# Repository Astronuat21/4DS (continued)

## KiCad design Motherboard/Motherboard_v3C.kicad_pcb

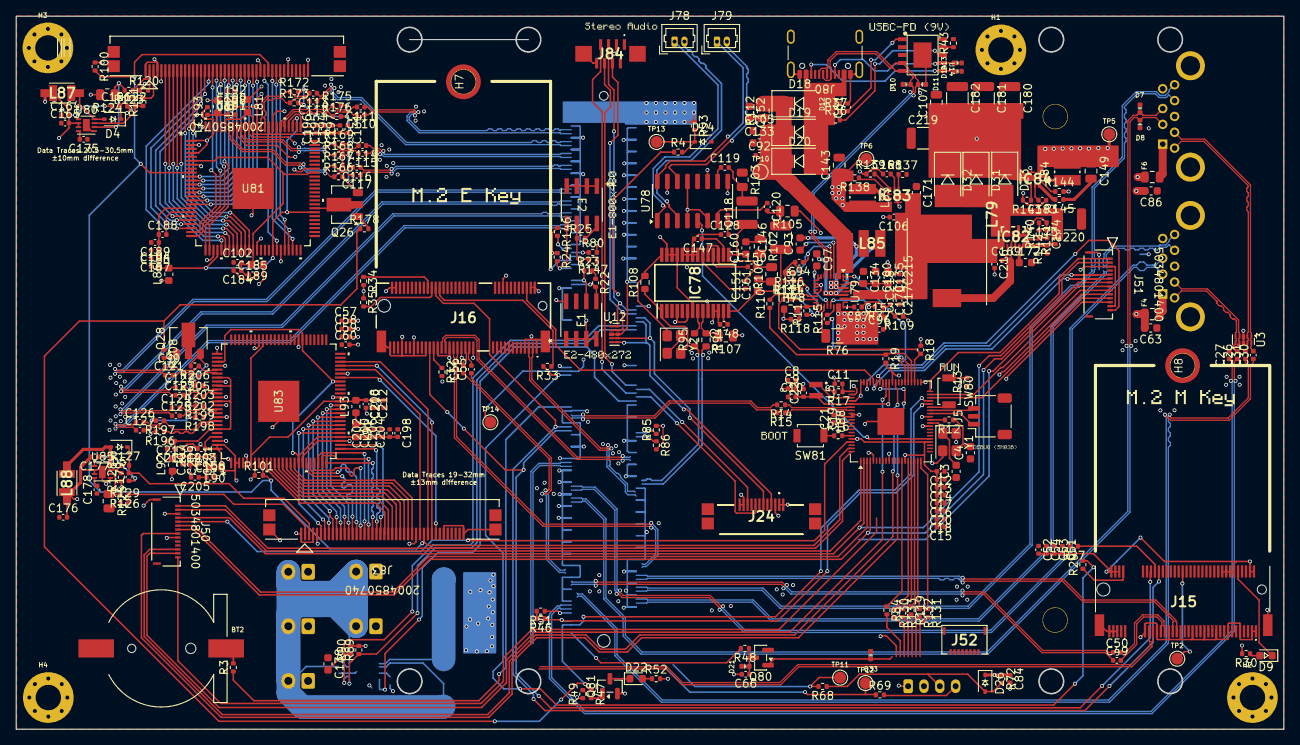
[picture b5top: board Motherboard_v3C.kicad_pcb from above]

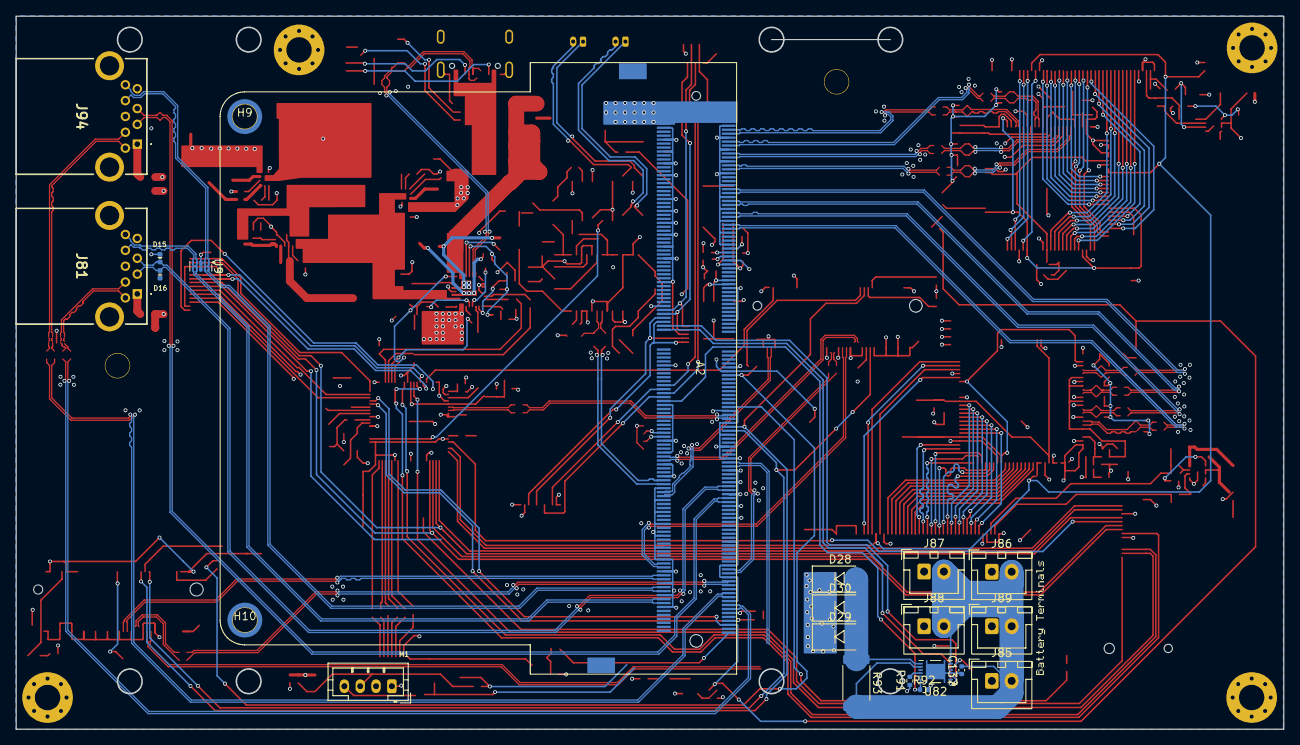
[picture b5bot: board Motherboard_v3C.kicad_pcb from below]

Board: 4 copper layers, 160.0 x 90.0 mm, 373 parts (23 on the bottom side), 327 nets.

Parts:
A2: LattePanda_Mu; LattePanda_Module_H8.0mm_Horizontal
BT2: Battery_Cell; Battery_Holder_CR1220_S8411-45R
C3, C4: 15pF; C_0603_1608Metric
C8, C9, C12, C13, C14, C15, C16, C17, C18, C20, C21, C26, C27, C30, C31, C52, C54, C58, C60, C84: 100nF; C_0402_1005Metric
C10, C11, C19, C22, C94: 4.7uF; C_0402_1005Metric
C49, C50, C55, C56, C169: 220nF; C_0402_1005Metric
C51, C53, C57, C59, C90, C96, C102, C104, C106, C108, C110, C111, C112, C113, C114, C115, C116, C117, C121, C122, C123, C124, C125, C126, C127, C131, C150, C153, C158, C164, C170, C177, C198, C207, C208, C215, C216, C217, C218: 10uF; C_0402_1005Metric
C61, C66, C119, C120, C128, C137, C147, C148, C151, C165, C166, C176, C179: 1uF; C_0402_1005Metric
C63, C86: 22uF; C_0603_1608Metric
C87: 1nF; C_0402_1005Metric
C92, C184, C185, C186, C187, C188, C189, C190, C191, C192, C193, C194, C195, C196, C197, C199, C200, C201, C202, C203, C204, C205, C206, C209, C210, C211, C212, C213, C214: 0.1uF; C_0402_1005Metric
C93, C97: 47nF; C_0603_1608Metric
C100, C105, C133, C134, C135: 10uF; C_0603_1608Metric
C107: 10uF; C_0805_2012Metric
C118, C146: 100uF; C_1210_3225Metric
C138: 0.47uF; C_0603_1608Metric
C143, C149: 22uF; C_0805_2012Metric
C152, C172: 2.2uF; C_0603_1608Metric
C160, C161: 0.022uF; C_0603_1608Metric
C168, C183: 1.2nF; C_0402_1005Metric
C171: 100nF; C_0603_1608Metric
C173: 39nF; C_0402_1005Metric
C174: 91pF; C_0402_1005Metric
C175, C178: 10nF; C_0402_1005Metric
C180, C181, C182, C219, C220: 47uF; C_1210_3225Metric
D4, D5, D26: 1N5819WS; D_SOD-323
D7, D8, D10, D11, D15, D16, D21, D33: ESD5V0B03; D_0402_1005Metric
D9, D22: LED_G; LED_0603_1608Metric
D12, D13, D14: PESD24VS1UL-N; D_0402_1005Metric
D18, D19, D20, D23, D28, D29, D30, D31, D32: SS54; D_SMA
D24: B5819WS-TP; D_SOD-323
E1, E2: 24AA025UIDT-I/SN; SOIC8-N_MC_MCH
F4, F6: 6V/2A; Fuse_0805_2012Metric
H1, H2, H3, H4: MountingHole_Pad; MountingHole_3.2mm_M3_Pad_Via
H7, H8: MountingHole_M2.0; MountingHole_3mm_M2_Pad_TopOnly
H9, H10: MountingHole_Pad; MountingHole_3mm_M2_Pad_TopOnly
IC78: PCM2704CDBR; SOP65P780X200-28N
IC82: TPS61288LRQQR; PTPS61288RQQR
IC83, IC84: TPS62903RPJR
J5: SM03B-SRSS-TB; JST_SH_SM03B-SRSS-TB_1x03-1MP_P1.00mm_Horizontal
J15: M.2 Socket M; MDT420M03001
J16: M.2 Socket E; MDT420E03001
J24: 200485-0710; 2004850710
J50, J51: 5034801400
J52: 503480-0800; 5034800800
J78: Speaker_L; Molex_PicoBlade_53047-0210_1x02_P1.25mm_Vertical
J79: Speaker_R; Molex_PicoBlade_53047-0210_1x02_P1.25mm_Vertical
J80: USB_C_Receptacle_USB2.0_16P; USB_C_Receptacle_GCT_USB4105-xx-A_16P_TopMnt_Horizontal
J81, J94: GSB311A41EU
J83, J90: 2004850740; CON_2004850740
J84: FFC2A33-08-T-R; FFC2A3308TR
J85: JST_XHP2_Battery1; JST_XH_B2B-XH-A_1x02_P2.50mm_Vertical
J86: JST_XHP2_Battery2; JST_XH_B2B-XH-A_1x02_P2.50mm_Vertical
J87: JST_XHP2_Battery3; JST_XH_B2B-XH-A_1x02_P2.50mm_Vertical
J88: JST_XHP2_Battery4; JST_XH_B2B-XH-A_1x02_P2.50mm_Vertical
J89: JST_XHP2_Battery5; JST_XH_B2B-XH-A_1x02_P2.50mm_Vertical
L5: 3.3uH; L_pol_2016
L79: 7443330220; WE-HCC_109021
L81, L82, L86, L89, L90, L91, L92, L93: BLM18RK601SN1D; L_0603_1608Metric
L83, L84: 74438336010HT
L85: 74438336022HT
L87, L88: LQH32CN220K23L; LQH32DN100K23L
M1: Fan_4pin; JST_PH_B4B-PH-K_1x04_P2.00mm_Vertical
Q26, Q28: 2SK3018-TP; SOT-89-3
Q80, Q81: 2N7002; SOT-23
R3, R12, R13, R16, R37, R47: 1k/1%; R_0402_1005Metric
R4, R18, R19, R22, R23, R24, R25, R34, R35, R36, R49, R85, R86, R91, R92, R100, R101, R109, R110, R111, R115: 10k/1%; R_0402_1005Metric
R14, R15: 27R; R_0402_1005Metric
R17: 33R/1%; R_0402_1005Metric
R27, R29, R32, R33: 0R/1%; R_0402_1005Metric
R30, R52, R53: 2.2k/1%; R_0402_1005Metric
R43: 6.8k/1%; R_0402_1005Metric
R46, R48, R69: 100R/1%; R_0402_1005Metric
R51, R80, R116, R138, R144: 100k/1%; R_0402_1005Metric
R68: 21.5K/1%; R_0402_1005Metric
R72: 4.7K/1%; R_0402_1005Metric
R76: 100R/1%; R_1206_3216Metric
R77: 4.7k/1%; R_0402_1005Metric
R84, R119: 150R/1%; R_0402_1005Metric
R89, R90: 5.1k/1%; R_0402_1005Metric
R93: 0.010R/1%; R_2512_6332Metric
R94, R95: 22R/1%; R_0603_1608Metric
R102, R106: 16R/1%; R_0805_2012Metric
R103, R105: 330R/1%; R_0805_2012Metric
R107: 1.5k/1%; R_0805_2012Metric
R108: 1M/1%; R_0603_1608Metric
R112: 2R/1%; R_0805_2012Metric
R113, R114: 127k/1%; R_0402_1005Metric
R117: 5.24k/1%; R_0402_1005Metric
R118: 30k/1%; R_0402_1005Metric
R120: 5.1R/1%; R_0402_1005Metric
R121, R122, R127, R128: 910k/1%; R_0402_1005Metric
R123, R126: 5k/1%; R_0402_1005Metric
R124, R125: 90.9k/1%; R_0805_2012Metric
R129: 10R/1%; R_0402_1005Metric
R130, R131, R132, R133: 47R/1%; R_0402_1005Metric
R137, R143: 40.2k/1%; R_0402_1005Metric
R139: 249k/1%; R_0402_1005Metric
R140: 39.2k/1%; R_0402_1005Metric
R141: 931k/1%; R_0402_1005Metric
R142: 48.7k/1%; R_0402_1005Metric
R145: 76.8k/1%; R_0402_1005Metric
R146, R147: 470R/1%; R_0402_1005Metric
R166, R167, R168, R169, R172, R173, R175, R176, R196, R197, R198, R199, R202, R203, R205, R206: 56k/1%; R_0402_1005Metric
R178, R208: 21.5k/1%; R_0402_1005Metric
SW80, SW81: SW_Push; SW_SPST_B3U-1000P
TH78: 10k/1%; R_0603_1608Metric
TP2, TP5, TP6, TP10, TP11, TP12, TP13, TP14: TestPoint; TestPoint_Pad_D1.5mm
U3, U9, U12: D3V3XA4B10LP-7; Diodes_UDFN-10_1x2.5mm_P0.5mm
U14: CH224K; ESSOP-10-1EP_3.9x5mm_P1.0mm_EP3.2x2.3
U78: PAM8406D; SOIC-16_3.9x9.9mm_P1.27mm
U79: BQ25798; Texas_RQM0029A_VQFN-29_4x4mm_P0.4mm
U80, U85: PAM2841G; DFN-8-1EP_2x2mm_P0.5mm_EP0.86x1.55mm
U81, U83: TFP401APZP; PZP100_5P2X5P2
U82: BQ27441DRZT-G1A; Texas_S-PDSO-N12
U88: RP2354B; QFN-80-1EP_10x10mm_P0.4mm_EP3.4x3.4mm
Y1, Y2: ABM8-272-T3; Crystal_SMD_3225-4Pin_3.2x2.5mm
kibuzzard-6A7CAF20: G***; kibuzzard-6A7CAF20
kibuzzard-6A7CAF29: G***; kibuzzard-6A7CAF29
kibuzzard-6A7CAF45: G***; kibuzzard-6A7CAF45
kibuzzard-6A7DF5CF: G***; kibuzzard-6A7DF5CF
kibuzzard-6A7DF57A: G***; kibuzzard-6A7DF57A
kibuzzard-6A9CE0FA: G***; kibuzzard-6A9CE0FA
kibuzzard-6A9CE105: G***; kibuzzard-6A9CE105
kibuzzard-6A74CEFD: G***; kibuzzard-6A74CEFD
kibuzzard-6A74CF1D: G***; kibuzzard-6A74CF1D
kibuzzard-6A760A01: G***; kibuzzard-6A760A01

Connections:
+1V1: C8.2, C9.2, C10.2, C22.1, L5.2, U88.10 (DVDD), U88.32 (DVDD), U88.51 (DVDD), U88.65 (VREG_FB)
+3V3: C12.2, C13.2, C14.2, C15.2, C16.2, C17.2, C18.2, C19.2, C20.2, C21.2, C51.2, C52.2, C53.2, C54.2, C57.2, C58.2, C59.2, C60.2, C143.1, C164.2, C165.2, C176.2, C177.2, E1.8, E2.8, IC78.7 (VDD), IC78.10 (VBUS), IC78.25 (TEST1), IC78.26 (TEST0), IC78.27 (~SSPND), IC83.3 (VOS), J15.2 (3.3V), J15.4 (3.3V), J15.12 (3.3V), J15.14 (3.3V), J15.16 (3.3V), J15.18 (3.3V), J15.70 (3.3V), J15.72 (3.3V), J15.74 (3.3V), J16.2 (3.3V), J16.4 (3.3V), J16.72 (3.3V), J16.74 (3.3V), J24.2, J50.3, J50.9, J51.3, J51.13, J83.4, J84.3, J90.4, L81.1, L82.1, L83.2, L86.1, L87.1, L87.3, L88.1, L88.3, L89.1, L90.1, L91.1, L92.1, L93.1, R17.2, R18.1, R19.2, R22.1, R23.2, R24.1, R25.2, R30.2, R34.2, R35.1, R52.2, R89.2, R90.2, R92.2, R100.1, R101.1, R107.1, R109.1, R138.2, R146.1, R147.1, TP6.1 (1_1), U78.4 (PVDDL), U78.6 (VDD), U78.9 (MODE), U78.13 (PVDDR), U80.2 (VIN), U80.3 (ENA), U81.2 (*PD), U81.3 (ST), U81.7 (*STAG), U81.99 (RSVD), U81.100 (OCK_INV), U83.2 (*PD), U83.3 (ST), U83.7 (*STAG), U83.99 (RSVD), U83.100 (OCK_INV), U85.2 (VIN), U85.3 (ENA), U88.5 (IOVDD), U88.15 (IOVDD), U88.24 (IOVDD), U88.29 (IOVDD), U88.41 (IOVDD), U88.50 (IOVDD), U88.59 (ADC_AVDD), U88.60 (IOVDD), U88.64 (VREG_VIN), U88.68 (USB_OTP_VDD), U88.69 (QSPI_IOVDD), U88.76 (IOVDD)
+5V: C63.2, C84.1, C86.2, C149.1, D26.1 (K), F4.1, F6.1, IC84.3 (VOS), L84.2, M1.2 (+), R72.1, R144.2, TP5.1 (1_1)
+9V: D12.1 (K), D18.2 (A), D19.2 (A), D20.2 (A), J80.A4 (VBUS), J80.A9 (VBUS), J80.B4 (VBUS), J80.B9 (VBUS), R36.1, R37.1
+BATT: A2.115 (VBAT), R3.1
/EXIO/Col1: J50.5, U88.77 (GPIO0)
/EXIO/Col2: J50.11, U88.78 (GPIO1)
/EXIO/Col3: J51.11, U88.38 (GPIO30)
/EXIO/Col4: J51.9, U88.39 (GPIO31)
/EXIO/LED_PWR_B: R131.1, U88.20 (GPIO20)
/EXIO/LED_PWR_G: R132.1, U88.19 (GPIO19)
/EXIO/LED_PWR_R: R119.1, U88.18 (GPIO18)
/EXIO/LED_WiFi_B: R133.1, U88.17 (GPIO17)
/EXIO/LED_WiFi_G: R130.1, U88.16 (GPIO16)
/EXIO/LED_WiFi_R: R84.1, U88.14 (GPIO15)
/EXIO/L_ADC_X: J50.13, U88.52 (GPIO41/ADC1)
/EXIO/L_ADC_Y: J50.12, U88.49 (GPIO40/ADC0)
/EXIO/PWR_Button: D33.1 (A1), J52.1, Q80.1 (G)
/EXIO/RPi_HALL_L: J50.1, U88.80 (GPIO3)
/EXIO/RPi_HALL_R: J51.1, U88.40 (GPIO32)
/EXIO/R_ADC_X: J51.5, U88.54 (GPIO43/ADC3)
/EXIO/R_ADC_Y: J51.6, U88.55 (GPIO44/ADC4)
/EXIO/Row1: J50.4, J51.2, U88.2 (GPIO5)
/EXIO/Row2: J50.7, J51.7, U88.4 (GPIO7)
/EXIO/Row3: J50.2, J51.8, U88.1 (GPIO4)
/EXIO/Row4: J50.6, J51.12, U88.3 (GPIO6)
/EXIO/Row5: J50.14, J51.10, U88.6 (GPIO8)
/EXIO/SL_BRI: J51.14, U88.58 (GPIO47/ADC7)
/EXIO/SL_VOL: J50.8, U88.53 (GPIO42/ADC2)
/Fan_Temp/FAN_1_PWM: A2.2 (FAN1_PWM), R69.1, TP12.1 (1_1)
/Fan_Temp/FAN_1_TAC: A2.4 (FAN1_TAC), R68.2, TP11.1 (1_1)
/LattePanda Module/AMP_L: C120.1, U78.7 (INL)
/LattePanda Module/AMP_R: C119.1, U78.10 (INR)
/LattePanda Module/Audio_D+: A2.76 (USB2_P7+), R94.2
/LattePanda Module/Audio_D-: A2.78 (USB2_P7-), R95.1
/LattePanda Module/Audio_DX+: IC78.9 (D+), R94.1, R107.2
/LattePanda Module/Audio_DX-: IC78.8 (D-), R95.2
/LattePanda Module/DDIB_INT: A2.124 (GPP_F13), J24.9
/LattePanda Module/DDIB_RST: A2.120 (GPP_F15), J24.7
/LattePanda Module/DDIB_TOUCH_SCL: A2.150 (I2C3_SCL), J24.3, U12.5, U12.6 (NC)
/LattePanda Module/DDIB_TOUCH_SDA: A2.152 (I2C3_SDA), J24.5, U12.4, U12.7 (NC)
/LattePanda Module/DDIB_TX0+: A2.217 (DDIB_TX0+), C90.1
/LattePanda Module/DDIB_TX0-: A2.215 (DDIB_TX0-), C121.1
/LattePanda Module/DDIB_TX1+: A2.211 (DDIB_TX1+), C122.1
/LattePanda Module/DDIB_TX1-: A2.209 (DDIB_TX1-), C123.1
/LattePanda Module/DDIB_TX2+: A2.205 (DDIB_TX2+), C124.1
/LattePanda Module/DDIB_TX2-: A2.203 (DDIB_TX2-), C125.1
/LattePanda Module/DDIB_TX3+: A2.199 (DDIB_TX3+), C126.1
/LattePanda Module/DDIB_TX3-: A2.197 (DDIB_TX3-), C127.1
/LattePanda Module/HSIO_0_TX+: A2.13 (HSIO0_TX+), C27.1
/LattePanda Module/HSIO_0_TX-: A2.15 (HSIO0_TX-), C26.1
/LattePanda Module/HSIO_1_TX+: A2.19 (HSIO1_TX+), C31.1
/LattePanda Module/HSIO_1_TX-: A2.21 (HSIO1_TX-), C30.1
/LattePanda Module/HSIO_2_RX+: A2.28 (HSIO2_RX+), J15.43 (PERp0/SATA-B-)
/LattePanda Module/HSIO_2_RX-: A2.30 (HSIO2_RX-), J15.41 (PERn0/SATA-B+)
/LattePanda Module/HSIO_2_TX+: A2.25 (HSIO2_TX+), C49.1
/LattePanda Module/HSIO_2_TX-: A2.27 (HSIO2_TX-), C50.1
/LattePanda Module/HSIO_3_RX+: A2.34 (HSIO3_RX+), J16.41 (PERp0)
/LattePanda Module/HSIO_3_RX-: A2.36 (HSIO3_RX-), J16.43 (PERn0)
/LattePanda Module/HSIO_3_TX+: A2.31 (HSIO3_TX+), C55.1
/LattePanda Module/HSIO_3_TX-: A2.33 (HSIO3_TX-), C56.1
/LattePanda Module/LOUT+: J78.1, U78.1 (+OUT_L)
/LattePanda Module/LOUT-: J78.2, U78.3 (-OUT_L)
/LattePanda Module/REFCLK0+: A2.85 (REFCLK0+), J15.53 (REFCLKn)
/LattePanda Module/REFCLK0-: A2.87 (REFCLK0-), J15.55 (REFCLKp)
/LattePanda Module/REFCLK3+: A2.88 (REFCLK3+), J16.47 (REFCLKp0)
/LattePanda Module/REFCLK3-: A2.90 (REFCLK3-), J16.49 (REFCLKn0)
/LattePanda Module/ROUT+: J79.1, U78.16 (+OUT_R)
/LattePanda Module/ROUT-: J79.2, U78.14 (-OUT_R)
/LattePanda Module/RP+: R14.1, U88.66 (USB_DM)
/LattePanda Module/RP-: R15.1, U88.67 (USB_DP)
/LattePanda Module/RPI_BAT_GPO: A2.118 (GPP_F16), R92.1, U82.12 (GPOUT)
/LattePanda Module/RPI_BAT_SCL: A2.146 (I2C4_SCL), R89.1, U82.1 (SDA)
/LattePanda Module/RPI_BAT_SDA: A2.148 (I2C4_SDA), R90.1, U82.2 (SCL)
/LattePanda Module/RPI_BAT_STAT: R109.2, U79.1 (STAT), U88.46 (GPIO37)
/LattePanda Module/RPR+: A2.111 (USB2_P5+), R14.2
/LattePanda Module/RPR-: A2.109 (USB2_P5-), R15.2
/LattePanda Module/RPi_5A_INT: R115.1, U88.45 (GPIO36)
/LattePanda Module/RPi_5A_SCL: R19.1, R110.1, U88.44 (GPIO35)
/LattePanda Module/RPi_5A_SDA: R18.2, R111.1, U88.43 (GPIO34)
/LattePanda Module/RPi_LCD_EN: J83.31, J90.31, R100.2, R101.2, U81.8 (SCDT), U81.9 (*PDO), U83.8 (SCDT), U83.9 (*PDO), U88.79 (GPIO2)
/LattePanda Module/RPi_PAM_LPWR: U78.5 (~MUTE), U88.25 (GPIO24)
/LattePanda Module/SLS_S3: A2.7 (SLS_S3), R46.1, U88.36 (GPIO28)
/LattePanda Module/SUSCLK_WIFI: A2.131 (SUSCLK), R29.2, R33.2
/LattePanda Module/SWCLK: J5.1, U88.33 (SWCLK)
/LattePanda Module/SWD: J5.3, U88.34 (SWDIO)
/LattePanda Module/TCP0_INT: A2.126 (GPP_F12), J84.6
/LattePanda Module/TCP0_RST: A2.122 (GPP_F14), J84.7
/LattePanda Module/TCP0_TOUCH_SCL: A2.154 (I2C2_SCL), J84.4, U12.2, U12.9 (NC)
/LattePanda Module/TCP0_TOUCH_SDA: A2.156 (I2C2_SDA), J84.5, U12.1, U12.10 (NC)
/LattePanda Module/TCP0_TX0+: A2.247 (TCP0_TX0+), C110.1
/LattePanda Module/TCP0_TX0-: A2.245 (TCP0_TX0-), C111.1
/LattePanda Module/TCP0_TX1+: A2.241 (TCP0_TXRX0+), C112.1
/LattePanda Module/TCP0_TX1-: A2.239 (TCP0_TXRX0-), C113.1
/LattePanda Module/TCP0_TX2+: A2.235 (TCP0_TX1+), C114.1
/LattePanda Module/TCP0_TX2-: A2.233 (TCP0_TX1-), C115.1
/LattePanda Module/TCP0_TX3+: A2.229 (TCP0_TXRX1+), C116.1
/LattePanda Module/TCP0_TX3-: A2.227 (TCP0_TXRX1-), C117.1
/LattePanda Module/USB_2_P7+: A2.70 (USB2_P4+), J16.3 (USB_D+)
/LattePanda Module/USB_2_P7-: A2.72 (USB2_P4-), J16.5 (USB_D-)
/LattePanda Module/WiFi_M2E_LED: J16.6 (~LED_1), U88.56 (GPIO45/ADC5)
/LattePanda Module/~PWR_SW: A2.1 (~PWRBTN), R48.2
/LattePanda Module/~USB_BOOT: R16.1, SW81.1
/M.2 E&M Key/CON_PCIE_TX_0+: C55.2, J16.35 (PETp0)
/M.2 E&M Key/CON_PCIE_TX_0-: C56.2, J16.37 (PETn0)
/M.2 E&M Key/CON_PCIE_TX_1+: C49.2, J15.49 (PETp0/SATA-A+)
/M.2 E&M Key/CON_PCIE_TX_1-: C50.2, J15.47 (PETn0/SATA-A-)
/M.2 E&M Key/~CLKREQE: J16.53 (~CLKREQ0), R32.1
/M.2 E&M Key/~CLKREQM: J15.52 (~CLKREQ), R27.1
/PSU/12VIn: C220.2, D23.2 (A), D31.2 (A), D32.2 (A), IC82.5 (VOUT), IC82.13 (VOUT), R141.2
/PSU/BAT+: C96.1, C153.1, D28.1 (K), D29.1 (K), D30.1 (K), R76.1, U79.22 (BAT), U79.23 (BAT)
/PSU/B_RAW: C137.2, J85.2, J86.2, J87.2, J88.2, J89.2, R93.2, U82.6 (BAT), U82.8 (SRP)
/PSU/CC1: D13.1 (K), J80.A5 (CC1), U14.7 (CC1)
/PSU/CC2: D14.1 (K), J80.B5 (CC2), U14.6 (CC2)
/PSU/PWR_C_D+: D11.2 (A2), J80.A6 (D+), J80.B6 (D+), U14.4 (DP), U79.6 (D+)
/PSU/PWR_C_D-: D10.2 (A2), J80.A7 (D-), J80.B7 (D-), U14.5 (DM), U79.7 (D-)
/PSU/SYS: C106.1, C170.1, C171.2, C215.1, C216.1, C217.1, C218.1, IC82.6 (EN), IC82.7 (VIN), IC82.14 (VIN), IC83.5 (EN), IC83.6 (VIN), L79.1, U79.25 (SYS)
/RGB/B0: J83.5, U83.30 (QE16)
/RGB/B1: J83.6, U83.31 (QE17)
/RGB/B2: J83.7, U83.32 (QE18)
/RGB/B3: J83.8, U83.33 (QE19)
/RGB/B4: J83.9, U83.34 (QE20)
/RGB/B5: J83.10, U83.35 (QE21)
/RGB/B6: J83.11, U83.36 (QE22)
/RGB/B7: J83.12, U83.37 (QE23)
/RGB/B8: J83.13, U83.20 (QE8)
/RGB/B9: J83.14, U83.21 (QE9)
/RGB/B10: J83.15, U83.22 (QE10)
/RGB/B11: J83.16, U83.23 (QE11)
/RGB/B12: J83.17, U83.24 (QE12)
/RGB/B13: J83.18, U83.25 (QE13)
/RGB/B14: J83.19, U83.26 (QE14)
/RGB/B15: J83.20, U83.27 (QE15)
/RGB/B16: J83.21, U83.10 (QE0)
/RGB/B17: J83.22, U83.11 (QE1)
/RGB/B18: J83.23, U83.12 (QE2)
/RGB/B19: J83.24, U83.13 (QE3)
/RGB/B20: J83.25, U83.14 (QE4)
/RGB/B21: J83.26, U83.15 (QE5)
/RGB/B22: J83.27, U83.16 (QE6)
/RGB/B23: J83.28, U83.17 (QE7)
/RGB/B-AVDD: C207.2, C209.1, C211.1, C213.1, C214.1, L92.2, U83.82 (AVDD), U83.84 (AVDD), U83.88 (AVDD), U83.95 (AVDD)
/RGB/B-DE: J83.30, U83.46 (DE)
/RGB/B-DVDD: C208.2, C210.1, C212.1, L93.2, U83.6 (DVDD), U83.38 (DVDD), U83.67 (DVDD)
/RGB/B-HS: J83.32, U83.48 (HSYNC)
/RGB/B-OVDD: C198.2, C200.1, C202.1, C204.1, C206.1, L91.2, U83.18 (OVDD), U83.29 (OVDD), U83.43 (OVDD), U83.57 (OVDD), U83.78 (OVDD)
/RGB/B-PCK: J83.34, U83.44 (ODCK)
/RGB/B-PVDD: C158.2, C199.1, C201.1, C203.1, C205.1, L90.2, U83.97 (PVDD)
/RGB/B-VS: J83.33, U83.47 (VSYNC)
/RGB/DDIB_CK+: C126.2, R197.1, U83.93 (RXC+)
/RGB/DDIB_CK-: C127.2, R196.1, U83.94 (RXC-)
/RGB/DDIB_D0+: C124.2, R199.1, U83.90 (RX0+)
/RGB/DDIB_D0-: C125.2, R198.1, U83.91 (RX0-)
/RGB/DDIB_D1+: C122.2, R203.1, U83.85 (RX1+)
/RGB/DDIB_D1-: C123.2, R202.1, U83.86 (RX1-)
/RGB/DDIB_D2+: C90.2, R206.1, U83.80 (RX2+)
/RGB/DDIB_D2-: C121.2, R205.1, U83.81 (RX2-)
/RGB/P0: J90.5, U81.30 (QE16)
/RGB/P1: J90.6, U81.31 (QE17)
/RGB/P2: J90.7, U81.32 (QE18)
/RGB/P3: J90.8, U81.33 (QE19)
/RGB/P4: J90.9, U81.34 (QE20)
/RGB/P5: J90.10, U81.35 (QE21)
/RGB/P6: J90.11, U81.36 (QE22)
/RGB/P7: J90.12, U81.37 (QE23)
/RGB/P8: J90.13, U81.20 (QE8)
/RGB/P9: J90.14, U81.21 (QE9)
/RGB/P10: J90.15, U81.22 (QE10)
/RGB/P11: J90.16, U81.23 (QE11)
/RGB/P12: J90.17, U81.24 (QE12)
/RGB/P13: J90.18, U81.25 (QE13)
/RGB/P14: J90.19, U81.26 (QE14)
/RGB/P15: J90.20, U81.27 (QE15)
/RGB/P16: J90.21, U81.10 (QE0)
/RGB/P17: J90.22, U81.11 (QE1)
/RGB/P18: J90.23, U81.12 (QE2)
/RGB/P19: J90.24, U81.13 (QE3)
/RGB/P20: J90.25, U81.14 (QE4)
/RGB/P21: J90.26, U81.15 (QE5)
/RGB/P22: J90.27, U81.16 (QE6)
/RGB/P23: J90.28, U81.17 (QE7)
/RGB/P-AVDD: C131.2, C194.1, C195.1, C196.1, C197.1, L81.2, U81.82 (AVDD), U81.84 (AVDD), U81.88 (AVDD), U81.95 (AVDD)
/RGB/P-DE: J90.34, U81.46 (DE)
/RGB/P-DVDD: C102.2, C184.1, C185.1, L89.2, U81.6 (DVDD), U81.38 (DVDD), U81.67 (DVDD)
/RGB/P-HS: J90.32, U81.48 (HSYNC)
/RGB/P-OVDD: C104.2, C186.1, C187.1, C188.1, C189.1, L86.2, U81.18 (OVDD), U81.29 (OVDD), U81.43 (OVDD), U81.57 (OVDD), U81.78 (OVDD)
/RGB/P-PCK: J90.30, U81.44 (ODCK)
/RGB/P-PVDD: C108.2, C190.1, C191.1, C192.1, C193.1, L82.2, U81.97 (PVDD)
/RGB/P-VS: J90.33, U81.47 (VSYNC)
/RGB/TMDS_CK+: C116.2, R167.1, U81.93 (RXC+)
/RGB/TMDS_CK-: C117.2, R166.1, U81.94 (RXC-)
/RGB/TMDS_D0+: C114.2, R169.1, U81.90 (RX0+)
/RGB/TMDS_D0-: C115.2, R168.1, U81.91 (RX0-)
/RGB/TMDS_D1+: C112.2, R173.1, U81.85 (RX1+)
/RGB/TMDS_D1-: C113.2, R172.1, U81.86 (RX1-)
/RGB/TMDS_D2+: C110.2, R176.1, U81.80 (RX2+)
/RGB/TMDS_D2-: C111.2, R175.1, U81.81 (RX2-)
/USB/CON_USB3_D_N: A2.73 (USB2_P2-), D16.2 (A2), J81.2 (D-)
/USB/CON_USB3_D_P: A2.75 (USB2_P2+), D15.2 (A2), J81.3 (D+)
/USB/CON_USB3_SSRX_N: A2.18 (HSIO0_RX-), J81.5 (STDA_SSRX-), U9.4, U9.7 (NC)
/USB/CON_USB3_SSRX_P: A2.16 (HSIO0_RX+), J81.6 (STDA_SSRX+), U9.5, U9.6 (NC)
/USB/CON_USB3_SSTX_N: C26.2, J81.8 (STDA_SSTX-), U3.4, U3.7 (NC)
/USB/CON_USB3_SSTX_P: C27.2, J81.9 (STDA_SSTX+), U3.5, U3.6 (NC)
/USB/CON_USB4_D_N: A2.67 (USB2_P1-), D8.2 (A2), J94.2 (D-)
/USB/CON_USB4_D_P: A2.69 (USB2_P1+), D7.2 (A2), J94.3 (D+)
/USB/CON_USB4_SSRX_N: A2.24 (HSIO1_RX-), J94.5 (STDA_SSRX-), U9.1, U9.10 (NC)
/USB/CON_USB4_SSRX_P: A2.22 (HSIO1_RX+), J94.6 (STDA_SSRX+), U9.2, U9.9 (NC)
/USB/CON_USB4_SSTX_N: C30.2, J94.8 (STDA_SSTX-), U3.1, U3.10 (NC)
/USB/CON_USB4_SSTX_P: C31.2, J94.9 (STDA_SSTX+), U3.2, U3.9 (NC)
/~PLT_RST: A2.105 (~PLTRST), J15.50 (~PERST), J16.52 (~PERST0)
/~PWR_LED/~PSON: A2.5 (SLS_S0), R47.1, R178.1, R208.1, U88.37 (GPIO29)
/~WAKE: A2.103 (~WAKE), J15.54 (~PEWAKE), J16.55 (~PEWAKE0)
GND: A2.11 (GND), A2.14 (GND), A2.17 (GND), A2.20 (GND), A2.23 (GND), A2.26 (GND), A2.29 (GND), A2.32 (GND), A2.35 (GND), A2.38 (GND), A2.41 (GND), A2.44 (GND), A2.47 (GND), A2.50 (GND), A2.53 (GND), A2.56 (GND), A2.59 (GND), A2.62 (GND), A2.65 (GND), A2.68 (GND), A2.71 (GND), A2.74 (GND), A2.77 (GND), A2.80 (GND), A2.83 (GND), A2.86 (GND), A2.89 (GND), A2.92 (GND), A2.95 (GND), A2.98 (GND), A2.101 (GND), A2.107 (GND), A2.110 (GND), A2.113 (GND), A2.116 (GND), A2.135 (GND), A2.136 (GND), A2.151 (GND), A2.158 (GND), A2.167 (GND), A2.170 (GND), A2.181 (GND), A2.182 (GND), A2.188 (GND), A2.189 (GND), A2.194 (GND), A2.195 (GND), A2.200 (GND), A2.201 (GND), A2.206 (GND), A2.207 (GND), A2.212 (GND), A2.213 (GND), A2.218 (GND), A2.219 (GND), A2.224 (GND), A2.225 (GND), A2.230 (GND), A2.231 (GND), A2.236 (GND), A2.237 (GND), A2.242 (GND), A2.243 (GND), A2.248 (GND), A2.249 (GND), A2.MP (Mountinge_Pads), BT2.2 (-), C3.1, C4.1, C8.1, C9.1, C10.1, C11.1, C12.1, C13.1, C14.1, C15.1, C16.1, C17.1, C18.1, C19.1, C20.1, C21.1, C22.2, C51.1, C52.1, C53.1, C54.1, C57.1, C58.1, C59.1, C60.1, C61.2, C63.1, C66.2, C84.2, C86.1, C87.1, C92.1, C94.2, C96.2, C100.1, C102.1, C104.1, C105.1, C106.2, C107.2, C108.1, C128.1, C131.1, C133.1, C134.1, C135.1, C137.1, C138.1, C143.2, C147.2, C148.2, C150.2, C151.2, C152.1, C153.2, C158.1, C165.1, C168.1, C170.2, C171.1, C172.2, C173.1, C174.1, C175.1, C176.1, C178.1, C180.1, C181.1, C182.1, C183.1, C184.2, C185.2, C186.2, C187.2, C188.2, C189.2, C190.2, C191.2, C192.2, C193.2, C194.2, C195.2, C196.2, C197.2, C198.1, C199.2, C200.2, C201.2, C202.2, C203.2, C204.2, C205.2, C206.2, C207.1, C208.1, C209.2, C210.2, C211.2, C212.2, C213.2, C214.2, C215.2, C216.2, C217.2, C218.2, C219.1, C220.1, D7.1 (A1), D8.1 (A1), D10.1 (A1), D11.1 (A1), D12.2 (A), D13.2 (A), D14.2 (A), D15.1 (A1), D16.1 (A1), D21.1 (A1), D24.2 (A), D33.2 (A2), E1.1, E1.2, E1.3, E1.4, E2.1, E2.2, E2.3, E2.4, H1.1 (1_1), H2.1 (1_1), H3.1 (1_1), H4.1 (1_1), H7.1 (1_1), H8.1 (1_1), H9.1 (1_1), H10.1 (1_1), IC78.4 (PSEL), IC78.6 (DGND), IC78.11 (ZGND), IC78.12 (AGNDL), IC78.17 (AGNDR), IC78.19 (PGND), IC78.21 (HOST), IC78.22 (HID0/MS), IC78.23 (HID1/MC), IC78.24 (HID2/MD), IC82.3 (PGND), IC82.10 (AGND), IC82.12 (PGND), IC83.4 (GND), IC84.4 (GND), J5.2, J5.MP (MountPin), J15.1 (GND), J15.3 (GND), J15.9 (GND), J15.15 (GND), J15.21 (GND), J15.27 (GND), J15.33 (GND), J15.39 (GND), J15.45 (GND), J15.51 (GND), J15.57 (GND), J15.71 (GND), J15.73 (GND), J15.75 (GND), J15.MP1, J15.MP2, J16.1 (GND), J16.7 (GND), J16.18 (GND), J16.33 (GND), J16.39 (GND), J16.45 (GND), J16.51 (GND), J16.57 (GND), J16.63 (GND), J16.69 (GND), J16.75 (GND), J16.MP1, J16.MP2, J24.1, J24.10, J24.G1 (GND_1), J24.G2 (GND_2), J24.MP1, J24.MP2, J24.MP3, J24.MP4, J50.10, J50.P1, J50.P2, J51.4, J51.P1, J51.P2, J52.2, J52.9, J52.10, J80.A1 (GND), J80.A12 (GND), J80.B1 (GND), J80.B12 (GND), J80.SH (SHIELD), J81.4 (GND), J81.7 (GND_DRAIN), J81.MH1, J81.MH2, J83.3, J83.29, J83.36, J83.G1, J83.G2, J83.P1, J83.P2, J83.P3, J83.P4, J84.1, J84.8, J84.MP1, J84.MP2, J85.1, J86.1, J87.1, J88.1, J89.1, J90.3, J90.29, J90.36, J90.G1, J90.G2, J90.P1, J90.P2, J90.P3, J90.P4, J94.4 (GND), J94.7 (GND_DRAIN), J94.MH1, J94.MH2, M1.1 (-), Q26.2 (S), Q28.2 (S), Q80.2 (S), Q81.2 (S), R13.1, R27.2, R32.2, R43.2, R49.1, R51.1, R77.1, R80.2, R85.2, R86.2, R91.1, R102.2, R103.1, R105.1, R106.2, R114.2, R116.2, R118.2, R120.1, R122.1, R124.2, R125.2, R128.1, R129.1, R137.2, R139.1, R142.1, R143.2, SW81.2, TH78.1, U3.3 (VSS), U3.8 (VSS), U9.3 (VSS), U9.8 (VSS), U12.3 (VSS), U12.8 (VSS), U14.0 (GND), U78.2 (PGNDL), U78.11 (GND), U78.15 (PGNDR), U79.10 (ACDRV2), U79.11 (ACDRV1), U79.13 (~CE), U79.27 (GND), U80.5 (GND), U80.9 (GND), U81.1 (DFO), U81.4 (PIXS), U81.5 (GND), U81.19 (OGND), U81.28 (OGND), U81.39 (GND), U81.45 (OGND), U81.58 (OGND), U81.68 (GND), U81.76 (OGND), U81.79 (AGND), U81.83 (AGND), U81.87 (AGND), U81.89 (AGND), U81.92 (AGND), U81.98 (PGND), U81.PAD, U82.3 (V_{SS}), U82.13 (PAD), U83.1 (DFO), U83.4 (PIXS), U83.5 (GND), U83.19 (OGND), U83.28 (OGND), U83.39 (GND), U83.45 (OGND), U83.58 (OGND), U83.68 (GND), U83.76 (OGND), U83.79 (AGND), U83.83 (AGND), U83.87 (AGND), U83.89 (AGND), U83.92 (AGND), U83.98 (PGND), U83.PAD, U85.5 (GND), U85.9 (GND), U88.62 (VREG_PGND), U88.81 (GND), Y1.2, Y1.4, Y2.2, Y2.4
LED_SCB+: C179.2, D5.1 (K), J83.2, R127.2
LED_SCB-: J83.1, R126.1, R129.2
LED_SCT+: C166.2, D4.1 (K), J90.2, R121.2
LED_SCT-: J90.1, R120.2, R123.1
unnamed: A2.171 (DDIB_DDC_SCL), E1.6, R23.1
unnamed: A2.169 (DDIB_DDC_SDA), E1.5, R22.2
unnamed: A2.183 (DDIB_HPD), R147.2
unnamed: A2.179 (TCP0_DDC_SCL), E2.6, R25.1
unnamed: A2.177 (TCP0_DDC_SDA), E2.5, R24.2
unnamed: A2.187 (TCP0_HPD), R146.2
unnamed: A2.185 (TCP1_HPD), R80.1
unnamed: A2.133 (~BIOS_SEL), R4.1, TP14.1 (1_1)
unnamed: A2.100 (~CLKREQ3), R86.1
unnamed: A2.102 (~CLKREQ4), R85.1
unnamed: BT2.1 (+), R3.2
unnamed: C4.2, R12.1, Y1.3
unnamed: C118.2, C119.2, R103.2
unnamed: C120.2, C146.2, R105.2
unnamed: C149.2, R145.1
unnamed: C152.2, R112.1
unnamed: C160.2, R102.1
unnamed: C161.2, R106.1
unnamed: C169.2, IC82.4 (SW), IC82.9 (SW), L79.2
unnamed: C173.2, R140.2
unnamed: D4.2 (A), L87.2, L87.4, U80.8 (SW)
unnamed: D5.2 (A), L88.2, L88.4, U85.8 (SW)
unnamed: D9.2 (A), R30.1
unnamed: D9.1 (K), J15.10 (DAS/~DSS/~LED1)
unnamed: C92.2, C105.2, C133.2, D18.1 (K), D19.1 (K), D20.1 (K), R112.2, TP10.1 (1_1), U79.2 (VBUS), U79.3 (VBUS)
unnamed: D22.2 (A), R52.1
unnamed: D22.1 (K), Q81.3 (D)
unnamed: D26.2 (A), M1.3 (Tacho), R68.1, R72.2
unnamed: D28.2 (A), D29.2 (A), D30.2 (A), R93.1, U82.7 (SRN)
unnamed: C148.1, IC78.13 (VCCL)
unnamed: C151.1, IC78.20 (VCCP)
unnamed: C147.1, IC78.16 (VCCR)
unnamed: C150.1, IC78.18 (VCOM)
unnamed: C146.1, C161.1, IC78.14 (VOUTL)
unnamed: C118.1, C160.1, IC78.15 (VOUTR)
unnamed: IC78.28 (XTI), R108.2, Y2.1
unnamed: IC78.1 (XTO), R108.1, Y2.3
unnamed: C169.1, IC82.8 (BST)
unnamed: C174.2, IC82.2 (COMP), R140.1
unnamed: IC82.1 (FB), IC82.15 (FB), R141.1, R142.2
unnamed: C172.1, IC82.11 (VCC)
unnamed: IC83.9 (FB/VSET), R139.2
unnamed: IC83.7 (MODE/S-CONF), R137.1
unnamed: IC83.1 (PG), R138.1
unnamed: C168.2, IC83.8 (SS/TR)
unnamed: IC83.2 (SW), L83.1
unnamed: IC84.9 (FB/VSET), R145.2
unnamed: IC84.7 (MODE/S-CONF), R143.1
unnamed: IC84.1 (PG), R144.1
unnamed: C183.2, IC84.8 (SS/TR)
unnamed: IC84.2 (SW), L84.1
unnamed: J15.38 (DEVSLP), TP2.1 (1_1)
unnamed: J15.68 (SUSCLK), R29.1
unnamed: J16.50 (SUSCLK), R33.1
unnamed: J16.56 (~W_DISABLE1), R34.1
unnamed: J16.54 (~W_DISABLE2), R35.2
unnamed: J52.3, R84.2
unnamed: J52.4, R130.2
unnamed: J52.5, R133.2
unnamed: J52.6, R119.2
unnamed: J52.7, R132.2
unnamed: J52.8, R131.2
unnamed: F4.2, J81.1 (VBUS)
unnamed: F6.2, J94.1 (VBUS)
unnamed: M1.4 (PWM), R69.2
unnamed: Q26.3 (D), R166.2, R167.2, R168.2, R169.2, R172.2, R173.2, R175.2, R176.2
unnamed: Q26.1 (G), R178.2
unnamed: Q28.3 (D), R196.2, R197.2, R198.2, R199.2, R202.2, R203.2, R205.2, R206.2
unnamed: Q28.1 (G), R208.2
unnamed: Q81.1 (G), R47.2, R49.2
unnamed: R13.2, SW80.1
unnamed: R46.2, R51.2
unnamed: R43.1, U14.9 (CFG1)
unnamed: R36.2, U14.8 (VBUS)
unnamed: C61.1, R37.2, U14.1 (VDD)
unnamed: C128.2, U78.8 (VREF)
unnamed: R76.2, U79.18 (BATP)
unnamed: C93.1, U79.4 (BTST1)
unnamed: C97.2, U79.19 (BTST2)
unnamed: R113.2, R114.1, R116.1, U79.17 (ILIM_HIZ)
unnamed: C100.2, C134.2, C135.2, U79.29 (PMID)
unnamed: R77.2, U79.20 (PROG)
unnamed: C94.1, R113.1, R117.1, U79.5 (REGN)
unnamed: R110.2, U79.14 (SCL)
unnamed: R111.2, U79.15 (SDA)
unnamed: C87.2, U79.24 (SDRV)
unnamed: C93.2, L85.1, U79.28 (SW1)
unnamed: C97.1, L85.2, U79.26 (SW2)
unnamed: R117.2, R118.1, TH78.2, U79.16 (TS)
unnamed: U79.8 (VAC2), U79.9 (VAC1)
unnamed: R115.2, U79.21 (~INT)
unnamed: C175.2, U80.4 (Comp)
unnamed: R123.2, R124.1, U80.6 (FB)
unnamed: R121.1, R122.2, U80.7 (OVP)
unnamed: R91.2, U82.10 (BIN)
unnamed: C138.2, U82.5 (V_{DD})
unnamed: C178.2, U85.4 (Comp)
unnamed: R125.1, R126.2, U85.6 (FB)
unnamed: R127.1, R128.2, U85.7 (OVP)
unnamed: SW80.2, U88.35 (RUN)
unnamed: C11.2, R17.1, U88.61 (VREG_AVDD)
unnamed: L5.1, U88.63 (VREG_LX)
unnamed: C3.2, U88.30 (XIN), Y1.1
unnamed: R12.2, U88.31 (XOUT)
unnamed: R16.2, U88.75 (~QSPI_SS)
PGND_B: C177.1, C179.1, U85.1 (PGND)
PGND_T: C164.1, C166.1, U80.1 (PGND)
PWR: C66.1, D21.2 (A2), Q80.3 (D), R48.1
VDC: A2.250 (VIN), A2.251 (VIN), A2.252 (VIN), A2.253 (VIN), A2.254 (VIN), A2.255 (VIN), A2.256 (VIN), A2.257 (VIN), A2.258 (VIN), A2.259 (VIN), A2.260 (VIN), C107.1, C180.2, C181.2, C182.2, C219.2, D23.1 (K), D31.1 (K), D32.1 (K), IC84.5 (EN), IC84.6 (VIN), R53.1
VPullup: D24.1 (K), R4.2, R53.2, TP13.1 (1_1)
